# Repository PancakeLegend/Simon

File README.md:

# Simon Memory Game
Simon memory game for #operationsnowball

Head over to the Wiki for more information and the [Assembly Guide](https://github.com/PancakeLegend/Simon/wiki).

***

Based on the [ATTiny13 Simon game](https://hackaday.io/project/18952-simon-game-with-attiny13) by Vojtěch Procházka

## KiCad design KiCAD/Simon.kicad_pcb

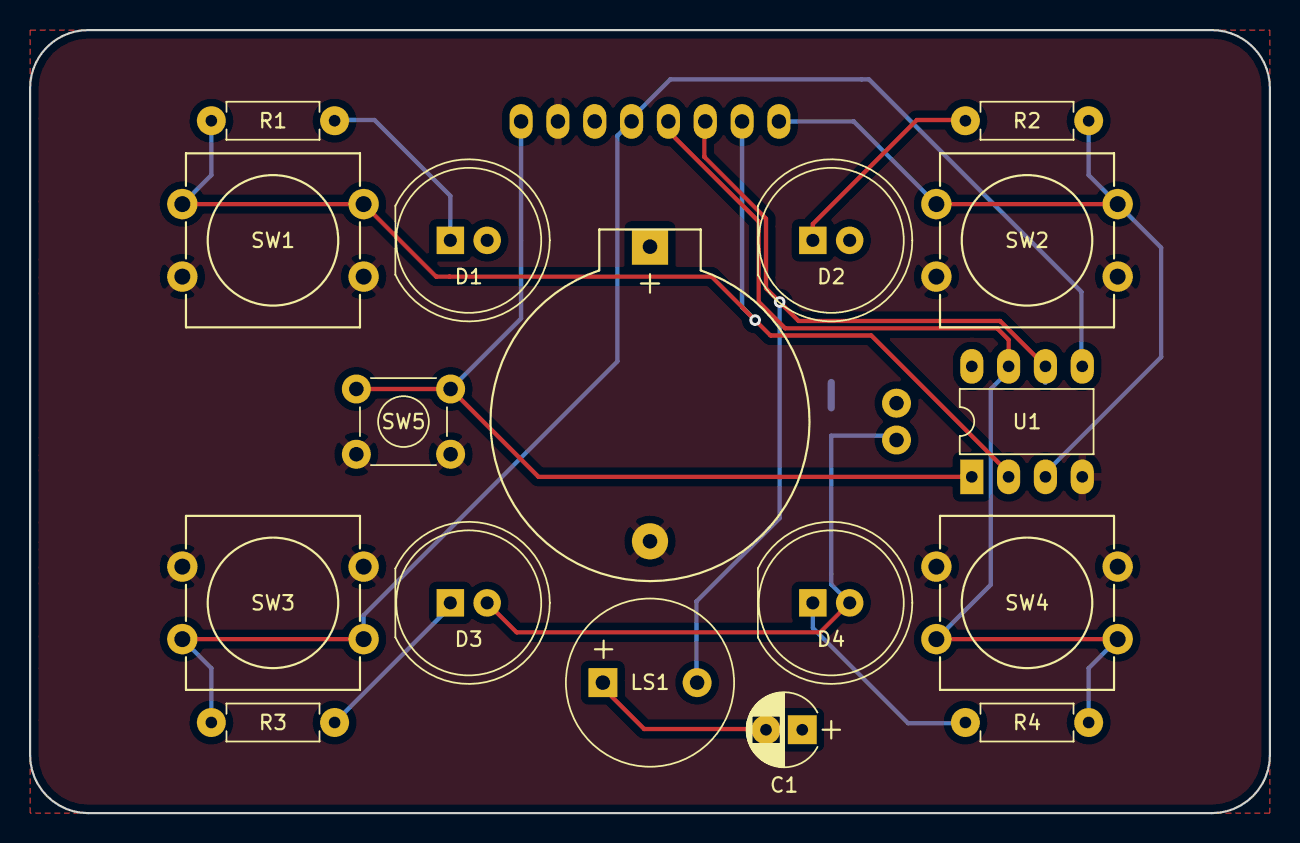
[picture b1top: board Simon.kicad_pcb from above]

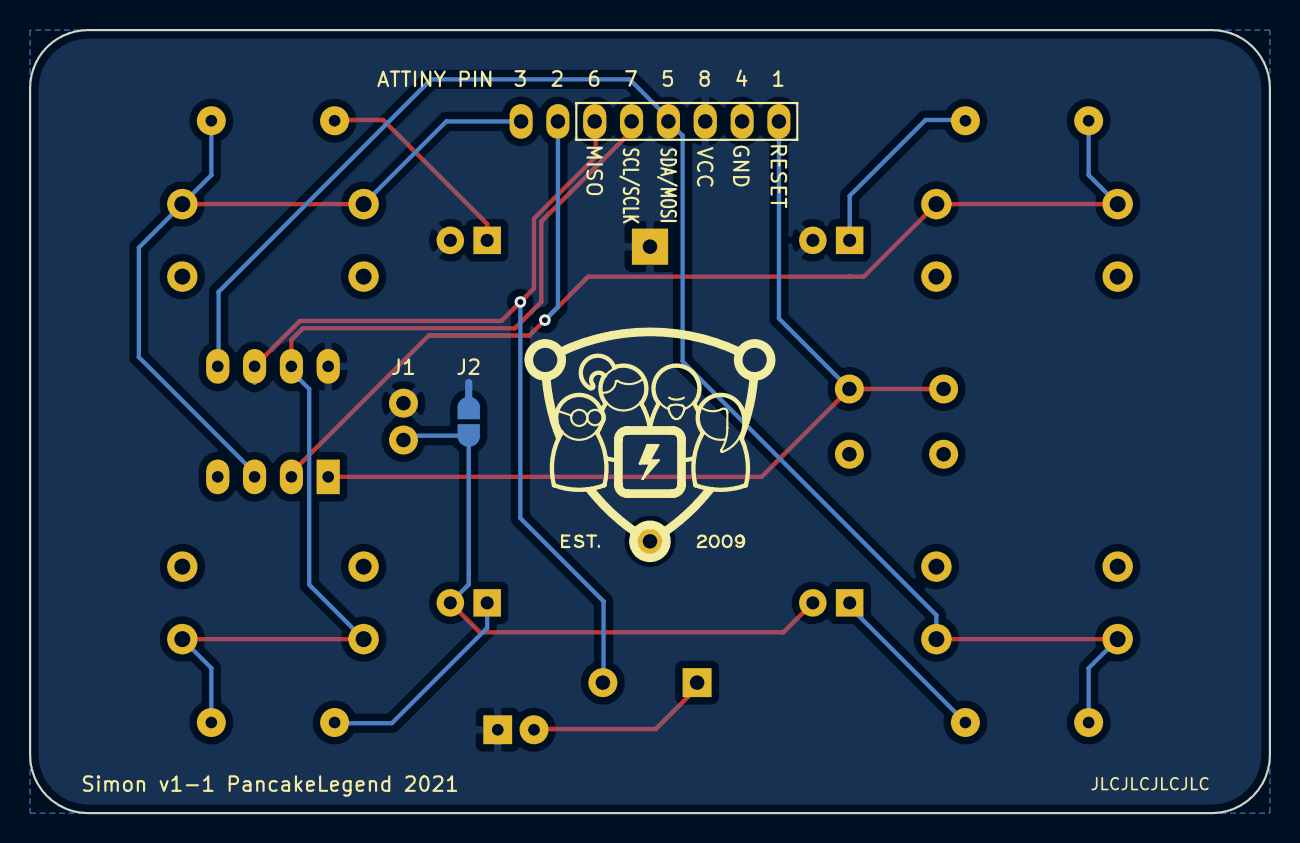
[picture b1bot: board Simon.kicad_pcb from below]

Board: 2 copper layers, 85.5 x 54.0 mm, 21 parts (3 on the bottom side), 14 nets.

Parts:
C1: CP; CP_Radial_D5.0mm_P2.50mm
D1, D2, D3, D4: LED; LED_D10.0mm
J1: Battery_Cell; CR2032-Plastic
J1#2: ProgJumper
J1#3: SAO_420; SAO_420_1x08
J2: SolderJumper; Jumper_Pad
L1: CCHS_Logo; CCHS_Logo_NoText
LS1: Speaker; Buzzer_12x9.5RM6.5
R1, R2, R3, R4: R; R_L6.3mm_D2.5mm_P8.5mm
SW1, SW2, SW3, SW4: SW_Push; SW_PUSH-12mm
SW5: SW_Push; SW_PUSH_6mm
U1: ATtiny13-20PU; DIP-8_W7.62mm_LongPads

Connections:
+BATT: C1.1, D1.2, D2.2, J1.1, J1#2.2, J1#3.3, J2.2, U1.8
GND: J1.2, J1#3.2, SW1.1, SW2.1, SW3.1, SW4.1, SW5.2, U1.4
unnamed: C1.2, LS1.1
unnamed: D1.1, R1.2
unnamed: D2.1, R2.2
unnamed: D3.1, R3.2
unnamed: D3.2, D4.2, J1#2.1, J2.1
unnamed: D4.1, R4.2
unnamed: J1#3.1, SW5.1, U1.1
unnamed: J1#3.4, R3.1, SW3.2, U1.5
unnamed: J1#3.5, R4.1, SW4.2, U1.7
unnamed: J1#3.6, LS1.2, U1.6
unnamed: J1#3.7, R1.1, SW1.2, U1.2
unnamed: J1#3.8, R2.1, SW2.2, U1.3

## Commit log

2022-05-14 KiCAD files added

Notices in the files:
README.md:
CC-BY-NC-SA
